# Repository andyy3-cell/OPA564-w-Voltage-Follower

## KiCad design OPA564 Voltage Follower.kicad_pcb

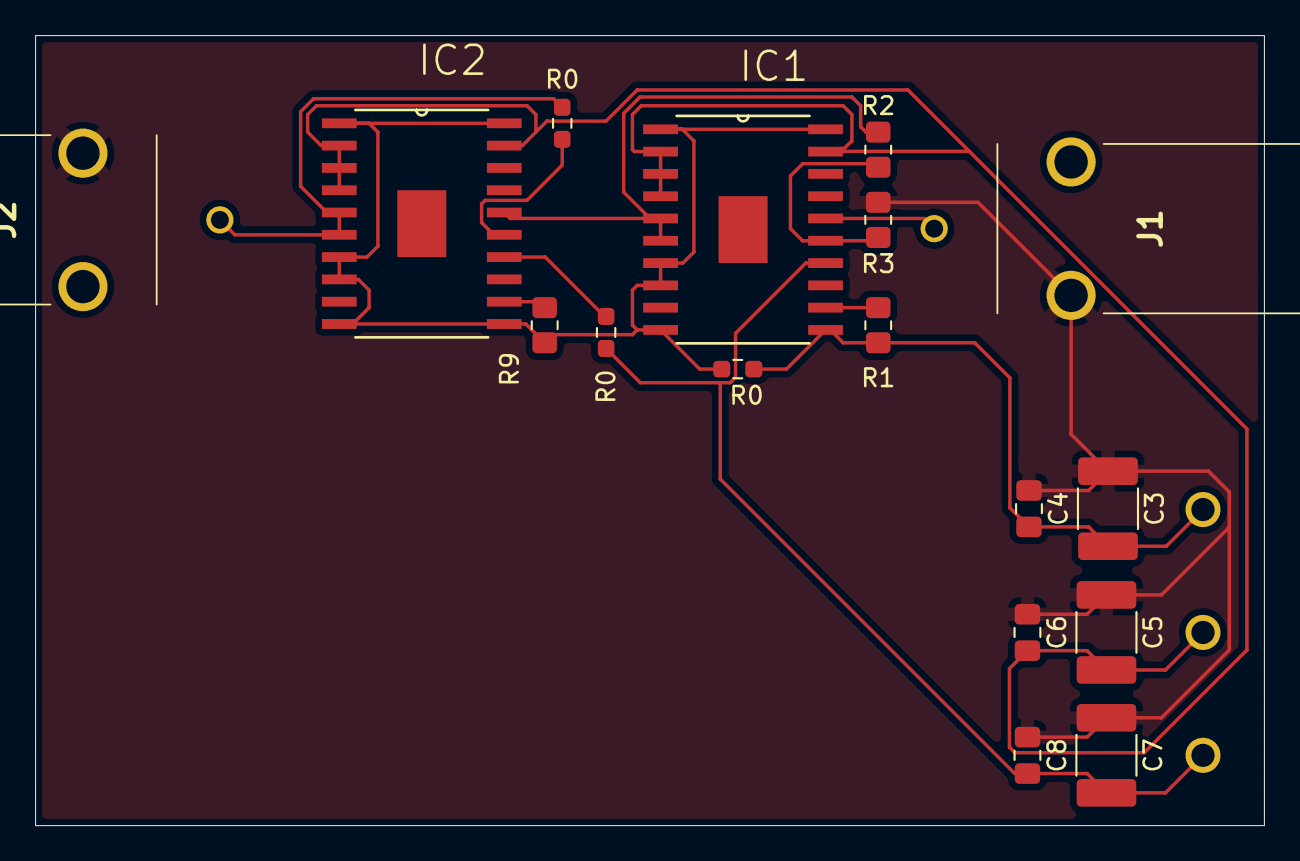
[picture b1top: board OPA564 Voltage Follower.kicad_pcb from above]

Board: 2 copper layers, 70.0 x 45.0 mm, 17 parts (0 on the bottom side), 10 nets.

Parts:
C3, C5, C7: 47 uC; C_1812_4532Metric_Pad1.57x3.40mm_HandSolder
C4, C6, C8: 0.1 uC; C_0805_2012Metric_Pad1.18x1.45mm_HandSolder
IC1, IC2: OPA564AIDWD; SOIC127P1040X265-21N
J1, J2: Conn_Coaxial; 731000154
R0, R0#2, R0#3: 0 Ohm; R_0603_1608Metric_Pad0.98x0.95mm_HandSolder
R1, R9: 14.2 kOhms; R_0805_2012Metric_Pad1.20x1.40mm_HandSolder
R2, R3: 1 kOhms; R_0805_2012Metric_Pad1.20x1.40mm_HandSolder

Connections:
+12 Volts: C5.2, C6.2, IC1.2 (V+_PWR_1), IC1.3 (V+_PWR_2), IC1.4 (V+_PWR_3), IC1.19 (V+), IC2.2 (V+_PWR_1), IC2.3 (V+_PWR_2), IC2.4 (V+_PWR_3), IC2.19 (V+)
-8 Volts: C7.2, C8.2, IC1.14 (VDIG), IC2.14 (VDIG), R0#2.1, R0#2.2
-12 Volts: C3.2, C4.2, IC1.1 (V-_1), IC1.7 (V-PWR_1), IC1.8 (V-PWR_2), IC1.10 (V-_2), IC1.11 (V-_3), IC1.20 (V-_4), IC2.1 (V-_1), IC2.7 (V-PWR_1), IC2.8 (V-PWR_2), IC2.10 (V-_2), IC2.11 (V-_3), IC2.20 (V-_4), R0.1, R0.2, R1.1, R9.1
GND: C3.1, C4.1, C5.1, C6.1, C7.1, C8.1, J1.2 (Ext), J2.2 (Ext), R3.1
unnamed: IC1.15 (-IN), R2.1, R3.2
unnamed: IC1.12 (ISET), R1.2
unnamed: IC2.5 (VOUT_1), IC2.6 (VOUT_2), IC2.15 (-IN), J2.1 (In), R0#3.1, R0#3.2
unnamed: IC2.12 (ISET), R9.2
Signal Input: IC1.16 (+IN), J1.1 (In)
Signal Output: IC1.5 (VOUT_1), IC1.6 (VOUT_2), IC2.16 (+IN), R2.2

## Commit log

2026-05-28 message
2026-05-29 A lot of silkscreen clearance issues :( but got the voltage follower done
2026-05-30 fixed everything
2026-06-01 version 1 i guess
2026-06-09 gerbers
